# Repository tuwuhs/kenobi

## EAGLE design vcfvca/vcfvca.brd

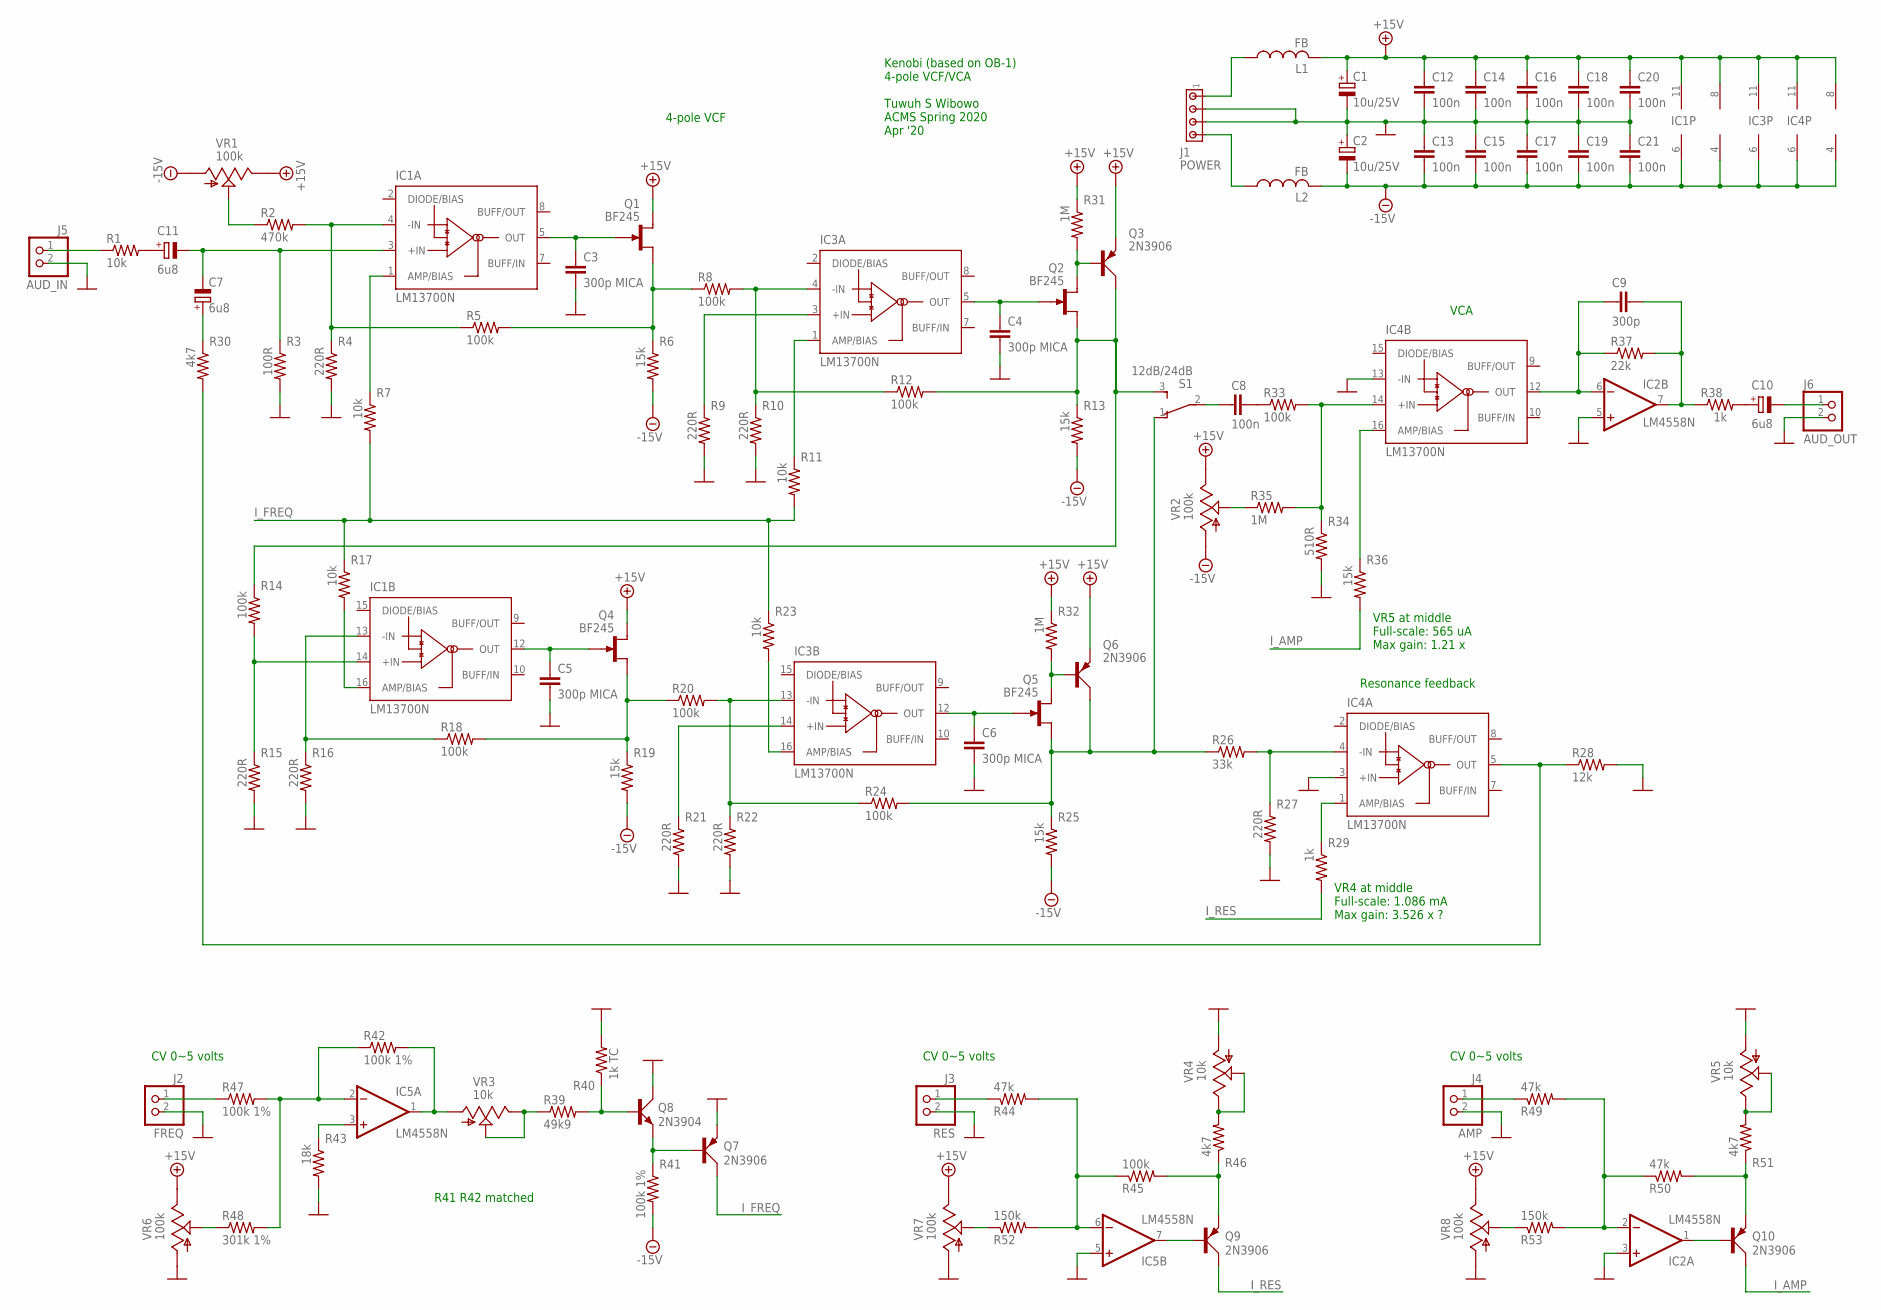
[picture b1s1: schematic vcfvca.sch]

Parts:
C1, C2: 10u/25V; E1,8-4
C3, C4, C5, C6: 300p MICA; C050-025X075
C7, C10, C11: 6u8; E1,8-4
C8, C12, C13, C14, C15, C16, C17, C18, C19, C20, C21: 100n; C050-025X075
C9: 300p; C050-025X075
IC1, IC3, IC4: LM13700N; DIL16
IC2, IC5: LM4558N; DIL08
J1: POWER; 1X4MTA
J2: FREQ; 1X02
J3: RES; 1X02
J4: AMP; 1X02
J5: AUD_IN; 1X02
J6: AUD_OUT; 1X02
L1, L2: FB; 0207/10
Q1, Q2, Q4, Q5: BF245; SOT54C
Q3, Q6, Q7, Q9, Q10: 2N3906; TO92D
Q8: 2N3904; TO92D
R1, R7, R11, R17, R23: 10k; 0207/10
R2: 470k; 0207/10
R3: 100R; 0207/10
R4, R9, R10, R15, R16, R21, R22, R27: 220R; 0207/10
R5, R8, R12, R14, R18, R20, R24, R33, R45: 100k; 0207/10
R6, R13, R19, R25, R36: 15k; 0207/10
R26: 33k; 0207/10
R28: 12k; 0207/10
R29, R38: 1k; 0207/10
R30, R46, R51: 4k7; 0207/10
R31, R32, R35: 1M; 0207/10
R34: 510R; 0207/10
R37: 22k; 0207/10
R39: 49k9; 0207/10
R40: 1k TC; 0207/10
R41, R42, R47: 100k 1%; 0207/10
R43: 18k; 0207/10
R44, R49, R50: 47k; 0207/10
R48: 301k 1%; 0207/10
R52, R53: 150k; 0207/10
S1: 12dB/24dB; TL3XPO
VR1, VR2: 100k; S63P
VR3, VR4, VR5: 10k; S63P
VR6, VR7, VR8: 100k; B64Y

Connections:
+15V: C1.+, C12.1, C14.1, C16.1, C18.1, C20.1, IC1.11 (V+), IC2.8 (V+), IC3.11 (V+), IC4.11 (V+), IC5.8 (V+), L1.2, Q1.D, Q3.E, Q4.D, Q6.E, R31.1, R32.1, VR1.E, VR2.E, VR6.E, VR7.E, VR8.E
-15V: C2.-, C13.2, C15.2, C17.2, C19.2, C21.2, IC1.6 (V-), IC2.4 (V-), IC3.6 (V-), IC4.6 (V-), IC5.4 (V-), L2.2, R6.2, R13.2, R19.2, R25.2, R41.2, VR1.A, VR2.A
GND: C1.-, C2.+, C3.2, C4.2, C5.2, C6.2, C12.2, C13.1, C14.2, C15.1, C16.2, C17.1, C18.2, C19.1, C20.2, C21.1, IC2.3 (+IN), IC2.5 (+IN), IC4.3 (+IN), IC4.13 (-IN), IC5.5 (+IN), J1.2, J1.3, J2.2, J3.2, J4.2, J5.2, J6.2, Q7.E, Q8.C, R3.2, R4.2, R9.2, R10.2, R15.2, R16.2, R21.2, R22.2, R27.2, R28.2, R34.2, R40.2, R43.2, VR4.A, VR5.A, VR6.A, VR7.A, VR8.A
I_AMP: Q10.C, R36.2
I_FREQ: Q7.C, R7.2, R11.2, R17.1, R23.1
I_RES: Q9.C, R29.2
unnamed: C4.1, IC3.5 (OUT), Q2.G
unnamed: C3.1, IC1.5 (OUT), Q1.G
unnamed: C5.1, IC1.12 (OUT), Q4.G
unnamed: C6.1, IC3.12 (OUT), Q5.G
unnamed: IC1.4 (-IN), R2.2, R4.1, R5.1
unnamed: IC1.1 (AMP/BIAS), R7.1
unnamed: Q1.S, R5.2, R6.1, R8.1
unnamed: C7.-, C11.-, IC1.3 (+IN), R3.1
unnamed: IC3.1 (AMP/BIAS), R11.1
unnamed: IC3.3 (+IN), R9.1
unnamed: IC3.4 (-IN), R8.2, R10.1, R12.1
unnamed: C7.+, R30.1
unnamed: IC1.14 (+IN), R14.2, R15.1
unnamed: IC1.13 (-IN), R16.1, R18.1
unnamed: IC4.4 (-IN), R26.2, R27.1
unnamed: Q4.S, R18.2, R19.1, R20.1
unnamed: Q2.S, Q3.C, R12.2, R13.1, R14.1, S1.3 (S)
unnamed: Q5.S, Q6.C, R24.2, R25.1, R26.1, S1.1 (O)
unnamed: IC3.13 (-IN), R20.2, R22.1, R24.1
unnamed: IC3.14 (+IN), R21.1
unnamed: IC4.1 (AMP/BIAS), R29.1
unnamed: IC1.16 (AMP/BIAS), R17.2
unnamed: IC3.16 (AMP/BIAS), R23.2
unnamed: IC4.5 (OUT), R28.1, R30.2
unnamed: Q5.D, Q6.B, R32.2
unnamed: Q2.D, Q3.B, R31.2
unnamed: C8.1, S1.2
unnamed: C8.2, R33.1
unnamed: IC4.14 (+IN), R33.2, R34.1, R35.2
unnamed: C9.1, IC2.6 (-IN), IC4.12 (OUT), R37.1
unnamed: R35.1, VR2.S
unnamed: IC4.16 (AMP/BIAS), R36.1
unnamed: R2.1, VR1.S
unnamed: C9.2, IC2.7 (OUT), R37.2, R38.1
unnamed: C10.+, R38.2
unnamed: C11.+, R1.2
unnamed: IC5.1 (OUT), R42.2, VR3.A
unnamed: R39.1, VR3.E, VR3.S
unnamed: Q8.B, R39.2, R40.1
unnamed: IC5.3 (+IN), R43.1
unnamed: IC5.2 (-IN), R42.1, R47.2, R48.2
unnamed: Q7.B, Q8.E, R41.1
unnamed: R46.2, VR4.E, VR4.S
unnamed: R51.2, VR5.E, VR5.S
unnamed: Q9.E, R45.2, R46.1
unnamed: IC5.7 (OUT), Q9.B
unnamed: IC5.6 (-IN), R44.2, R45.1, R52.2
unnamed: Q10.E, R50.2, R51.1
unnamed: IC2.1 (OUT), Q10.B
unnamed: J2.1, R47.1
unnamed: IC2.2 (-IN), R49.2, R50.1, R53.2
unnamed: J4.1, R49.1
unnamed: R48.1, VR6.S
unnamed: J5.1, R1.1
unnamed: J3.1, R44.1
unnamed: C10.-, J6.1
unnamed: R52.1, VR7.S
unnamed: R53.1, VR8.S
unnamed: J1.1, L1.1
unnamed: J1.4, L2.1

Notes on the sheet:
R41 R42 matched
CV 0~5 volts
VR5 at middle Full-scale: 565 uA Max gain: 1.21 x
VR4 at middle Full-scale: 1.086 mA Max gain: 3.526 x ?
4-pole VCF
VCA
Resonance feedback
Kenobi (based on OB-1) 4-pole VCF/VCA Tuwuh S Wibowo ACMS Spring 2020 Apr '20

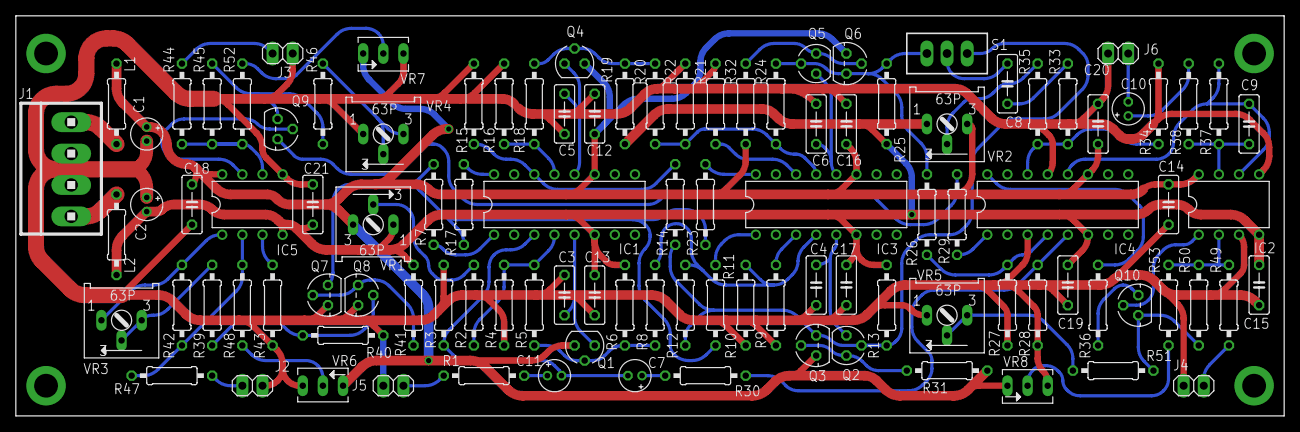
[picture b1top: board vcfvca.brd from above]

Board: 2 copper layers, 160.0 x 50.5 mm, 106 parts (0 on the bottom side), 66 nets.

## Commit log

2020-04-01 Draw schematics for the filter and VCA, excluding control
2020-04-01 Minor changes
2020-04-01 Add VCF freq and res control current generator
2020-04-01 Fix .gitignore: include eagle.epf project file
2020-04-02 Add circuit analysis writeup
2020-04-02 Finished drawing the schematics. Adapted RES current source for AMP.
2020-04-02 Run and approve ERC
2020-04-02 Fix VCA scale and feedback resistor
2020-04-02 Minor tweak
2020-04-02 Fix component value. Export to image
2020-04-02 Generate PCB file
2020-04-02 Start board placement
2020-04-02 Done placement
2020-04-02 Routed the signals
2020-04-02 Finsihed routing!
2020-04-02 Clear DRC errors
2020-04-03 Tidy up overlay
2020-04-03 Add signature, done! (for now)
2020-04-03 Minor fixes. Add images.
2020-04-03 Minor fixes
2020-04-21 Add ferrite bead, reroute
2020-04-22 Clean up routing
2020-04-22 Move PCB to 0,0
2020-04-22 Export images
2020-04-23 VCF/VCA: revision for final submission
